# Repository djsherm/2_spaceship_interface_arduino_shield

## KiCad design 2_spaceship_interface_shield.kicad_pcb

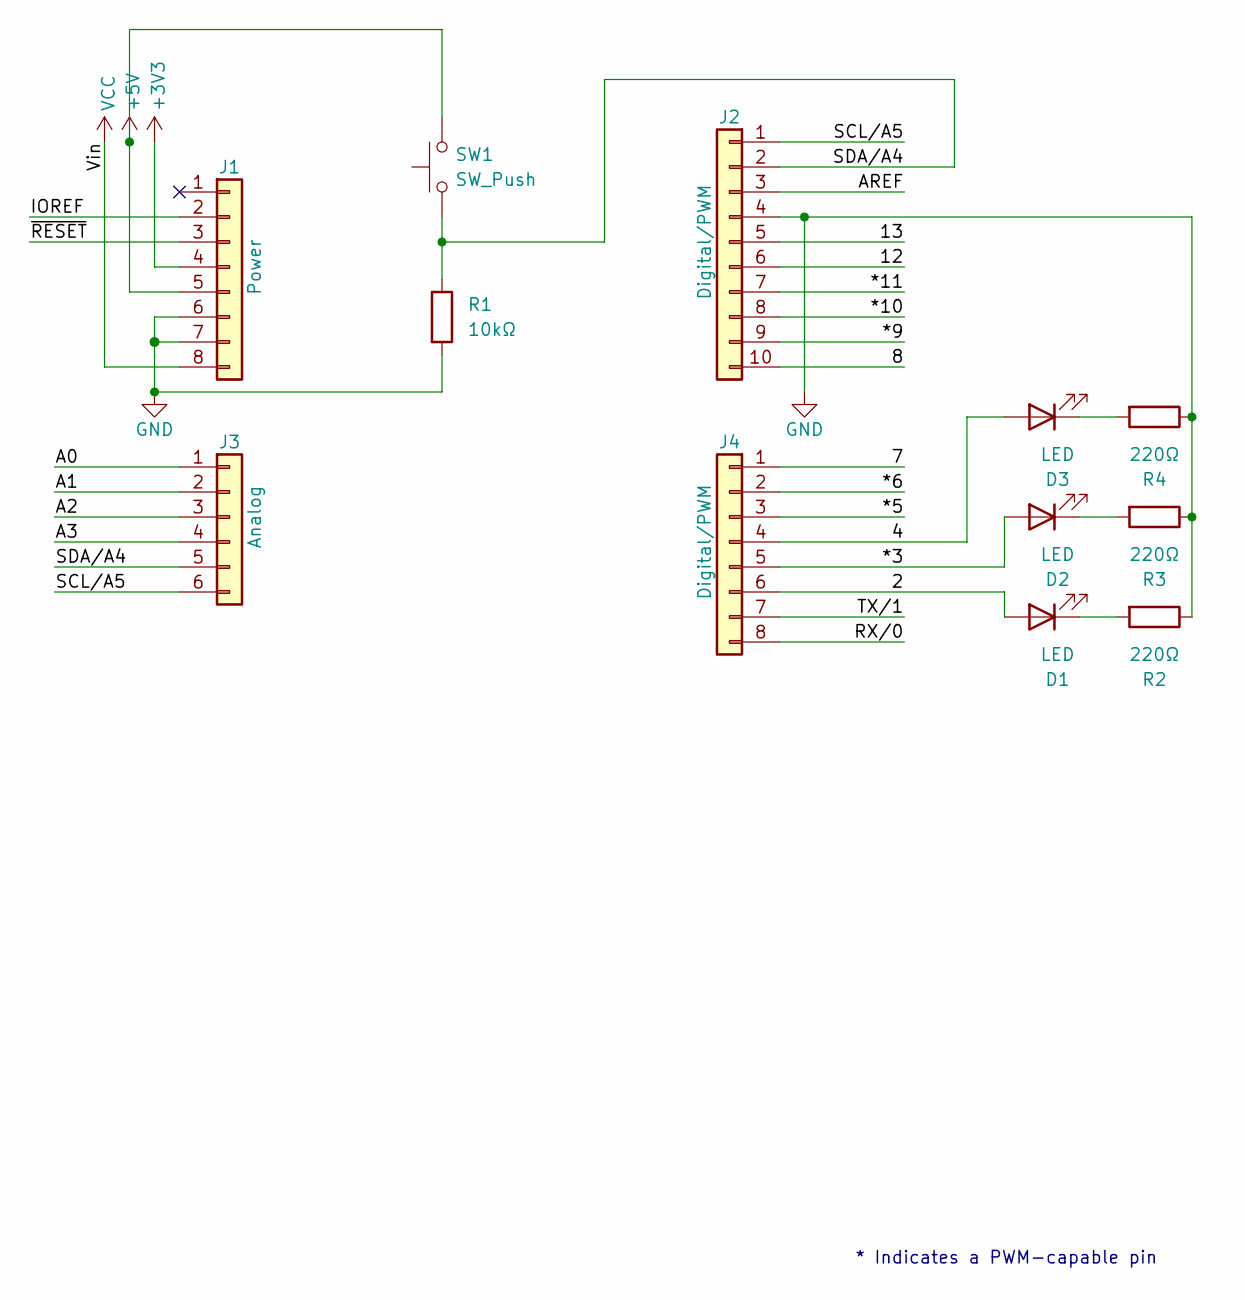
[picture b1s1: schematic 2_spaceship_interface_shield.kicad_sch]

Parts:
D1, D2, D3: LED; LED_D5.0mm
J1: Power; PinSocket_1x08_P2.54mm_Vertical
J2: Digital/PWM; PinSocket_1x10_P2.54mm_Vertical
J3: Analog; PinSocket_1x06_P2.54mm_Vertical
J4: Digital/PWM; PinSocket_1x08_P2.54mm_Vertical
R1: 10kΩ; R_Axial_DIN0207_L6.3mm_D2.5mm_P10.16mm_Horizontal
R2, R3, R4: 220Ω; R_Axial_DIN0207_L6.3mm_D2.5mm_P10.16mm_Horizontal
SW1: SW_Push; TS02 push button

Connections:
+3V3: J1.4
+5V: J1.5, SW1.2
/2: D1.2 (A), J4.6
/4: D3.2 (A), J4.4
/7: J4.1
/8: J2.10
/12: J2.6
/13: J2.5
/*3: D2.2 (A), J4.5
/*5: J4.3
/*6: J4.2
/*9: J2.9
/*10: J2.8
/*11: J2.7
/A0: J3.1
/A1: J3.2
/A2: J3.3
/A3: J3.4
/AREF: J2.3
/IOREF: J1.2
/RX/0: J4.8
/SCL/A5: J2.1, J3.6
/SDA/A4: J2.2, J3.5, R1.1, SW1.1
/TX/1: J4.7
/~RESET: J1.3
GND: J1.6, J1.7, J2.4, R1.2, R2.1, R3.1, R4.1
unnamed: D1.1 (K), R2.2
unnamed: D2.1 (K), R3.2
unnamed: D3.1 (K), R4.2
VCC: J1.8

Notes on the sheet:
* Indicates a PWM-capable pin

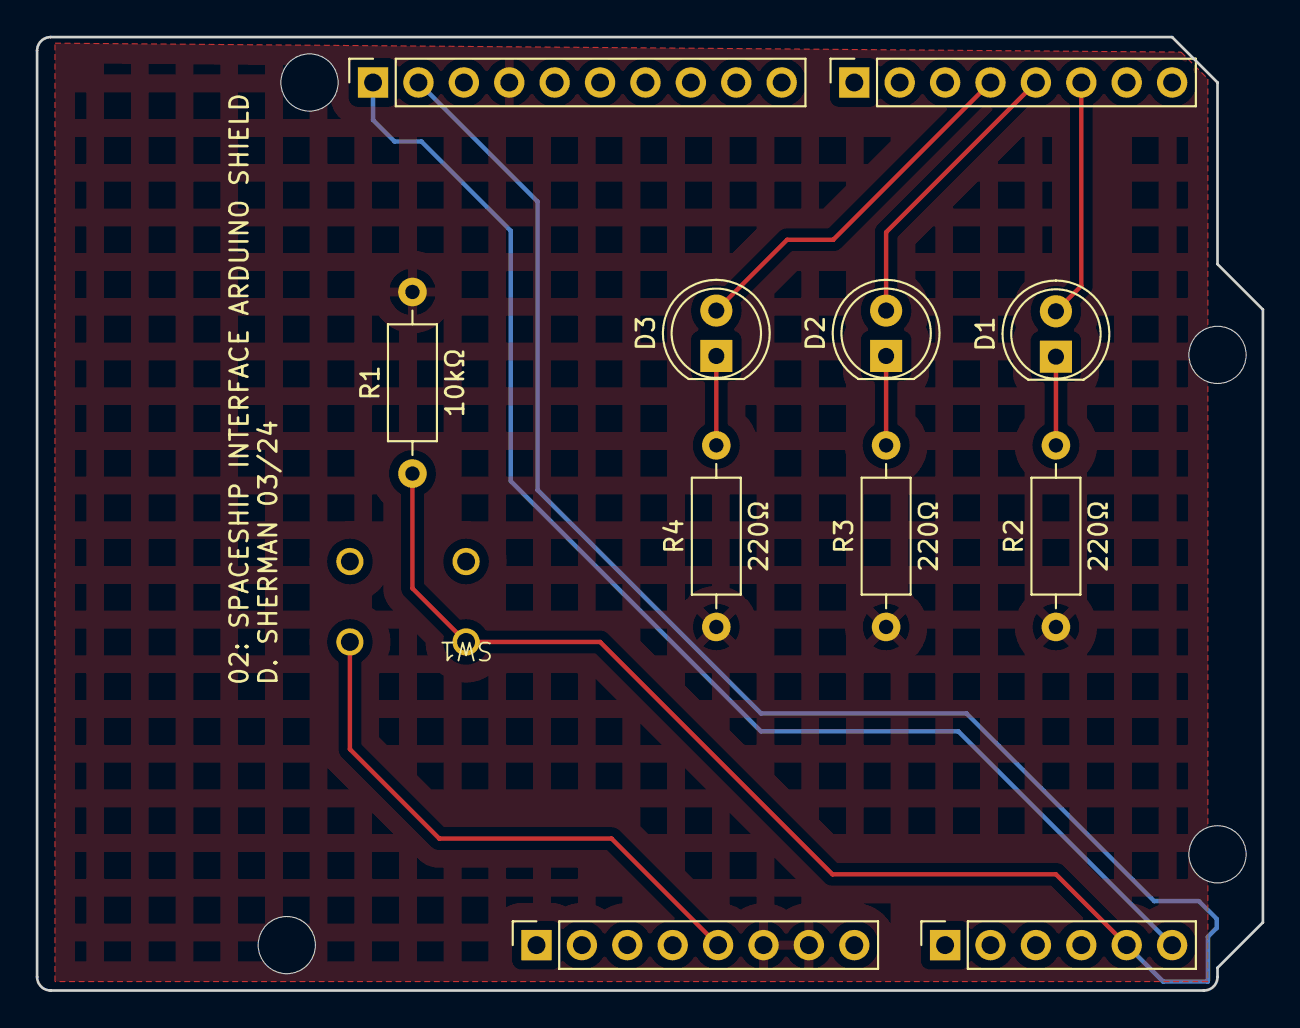
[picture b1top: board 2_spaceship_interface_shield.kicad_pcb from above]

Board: 2 copper layers, 68.6 x 53.3 mm, 16 parts (0 on the bottom side), 10 nets.

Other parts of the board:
MH1, MH2, MH3, MH4: MountingHole_3.2mm

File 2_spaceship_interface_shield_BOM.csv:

"Id";"Designator";"Footprint";"Quantity";"Designation";"Supplier and ref";
1;"J1";"PinSocket_1x08_P2.54mm_Vertical";1;"Power";;;
2;"J3";"PinSocket_1x06_P2.54mm_Vertical";1;"Analog";;;
3;"J2";"PinSocket_1x10_P2.54mm_Vertical";1;"Digital/PWM";;;
4;"J4";"PinSocket_1x08_P2.54mm_Vertical";1;"Digital/PWM";;;
5;"R1";"R_Axial_DIN0207_L6.3mm_D2.5mm_P10.16mm_Horizontal";1;"10kΩ";;;
6;"R3,R4,R2";"R_Axial_DIN0207_L6.3mm_D2.5mm_P10.16mm_Horizontal";3;"220Ω";;;
7;"D1,D2,D3";"LED_D5.0mm";3;"LED";;;
8;"SW1";"TS02 push button";1;"SW_Push";;;
